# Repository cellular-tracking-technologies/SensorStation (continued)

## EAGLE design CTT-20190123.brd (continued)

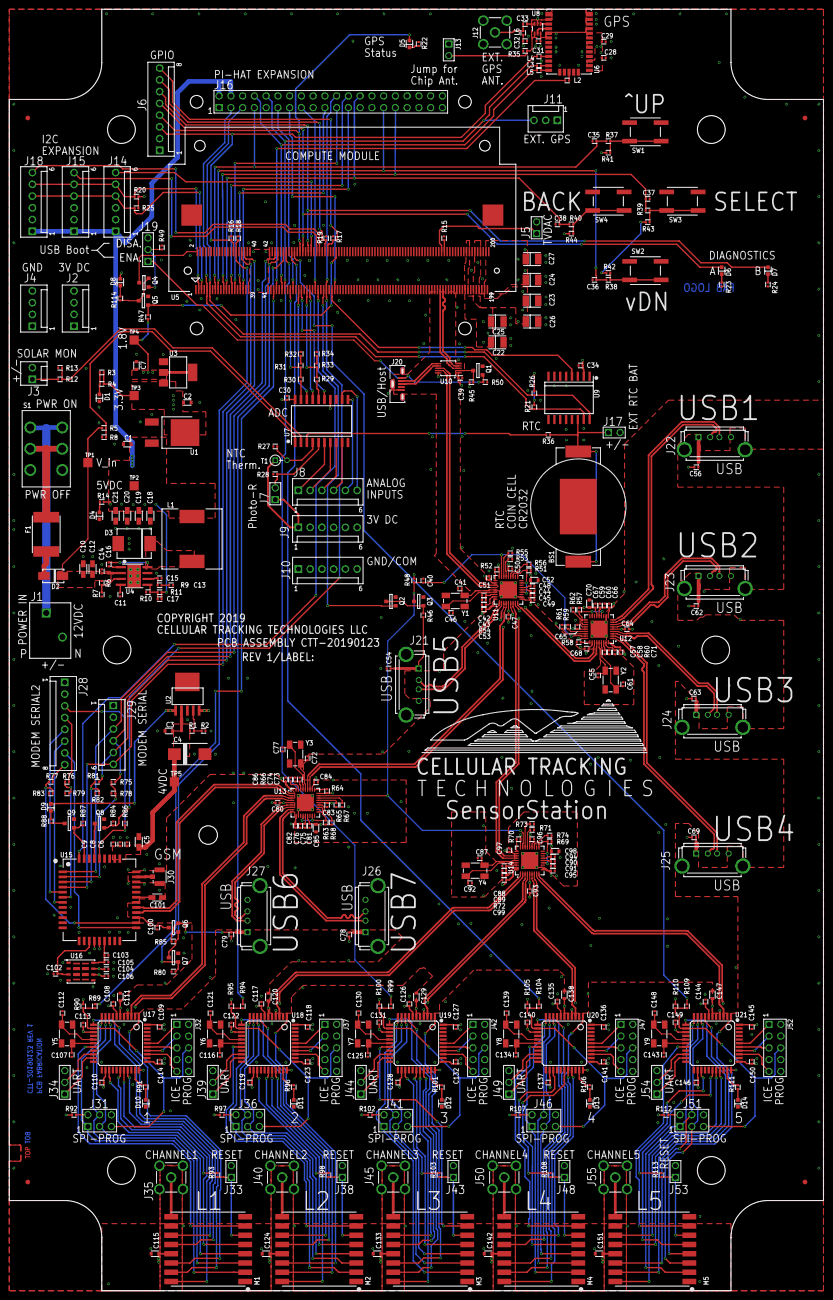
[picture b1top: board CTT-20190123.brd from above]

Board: 4 copper layers, 175.5 x 276.5 mm, 412 parts (0 on the bottom side), 334 nets.

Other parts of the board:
U$1: HEX_8MM
U$2: CTT-LOGO_W2INCH
U$138, U$140, U$247, U$248: FIDUCIAL
U$240, U$241, U$242, U$243, U$244, U$245: FUNCUBE_ENVELOPE_VERT
U$246: PI_HAT_OUTLINE
U$249: BORDER_C_DOCU

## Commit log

2019-08-16 Adding first production version of SensorStation
2019-08-16 Adding PDF of SensorStation Schematic
2019-08-16 Picture of SensorStation
